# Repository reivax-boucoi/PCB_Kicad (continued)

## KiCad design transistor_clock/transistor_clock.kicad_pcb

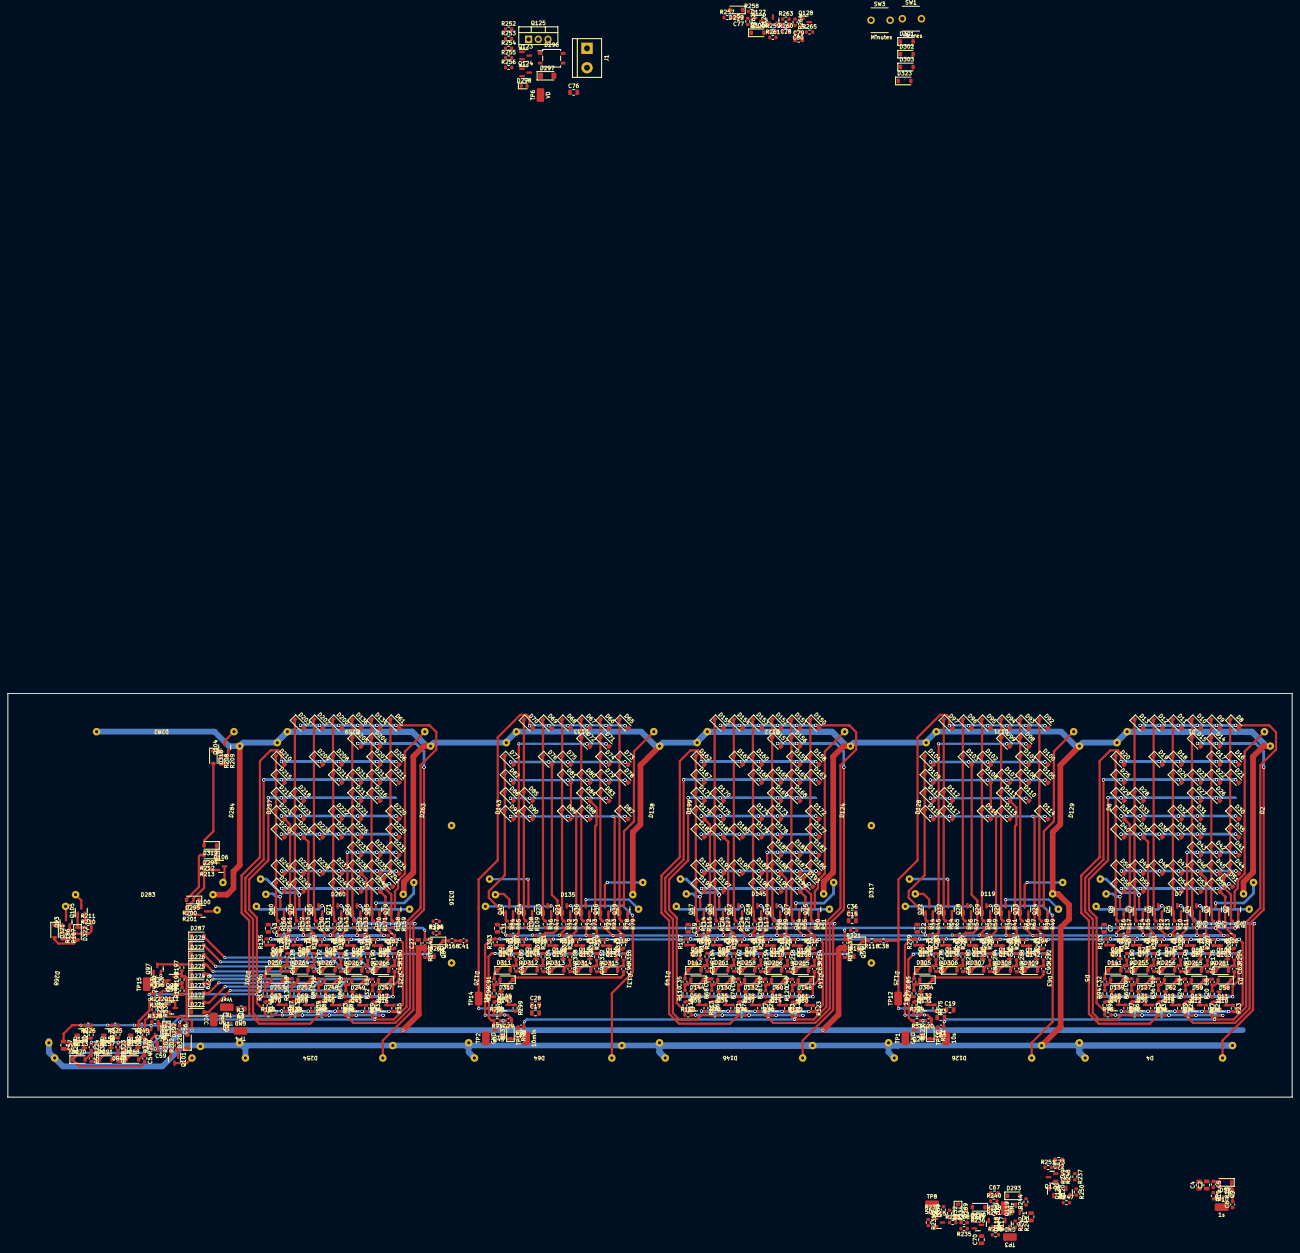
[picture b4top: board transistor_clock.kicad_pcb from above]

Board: 2 copper layers, 336.5 x 105.8 mm, 907 parts (0 on the bottom side), 423 nets.

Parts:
C1, C2, C4, C7, C13, C15, C17, C19, C22, C27, C28, C31, C36, C39, C43, C57, C58, C67, C72, C76, C79: 10u; C_0805_2012Metric
C3, C8, C9, C10, C11, C12, C14, C16, C18, C23, C24, C25, C26, C32, C33, C34, C35, C40, C44, C45, C46, C47, C48, C49, C50, C51, C52, C53, C54, C55, C62, C63, C64, C85, C86, C87, C88, C89, C90, C91, C92, C93, C94, C95, C96: 1n; C_0603_1608Metric
C5, C6, C20, C21, C29, C30, C37, C38, C41, C42, C56, C59, C68, C69, C73, C80: 100n; C_0603_1608Metric
C70, C71: 1u; C_0805_2012Metric
C77: 10n; C_0805_2012Metric
C78: 220p; C_0805_2012Metric
D1, D2, D3, D4, D5, D6, D7, D63, D64, D119, D120, D121, D122, D124, D125, D126, D128, D129, D131, D133, D135, D138, D140, D143, D145, D146, D149, D199, D201, D251, D254, D257, D259, D260, D263, D268, D279, D280, D282, D283, D284, D316, D317: LED; LED_filament_38mm
D8, D9, D10, D11, D12, D13, D14, D15, D16, D17, D18, D19, D20, D21, D22, D23, D24, D25, D26, D27, D28, D29, D30, D31, D32, D33, D34, D35, D36, D37, D38, D39, D40, D41, D42, D43, D44, D45, D46, D47, D48, D49, D50, D51, D52, D53, D54, D55, D56, D57, D58, D59, D60, D61, D62, D65, D66, D67, D68, D69, D70, D71, D72, D73, D74, D75, D76, D77, D78, D79, D80, D81, D82, D83, D84, D85, D86, D87, D88, D89, D90, D91, D92, D93, D94, D95, D96, D97, D98, D99, D100, D101, D102, D103, D104, D105, D106, D107, D108, D109, D110, D111, D112, D113, D114, D115, D116, D117, D118, D123, D127, D130, D132, D134, D136, D137, D139, D141, D142, D144, D147, D148, D150, D151, D152, D153, D154, D155, D156, D157, D158, D159, D160, D161, D162, D163, D164, D165, D166, D167, D168, D169, D170, D171, D172, D173, D174, D175, D176, D177, D178, D179, D180, D181, D182, D183, D184, D185, D186, D187, D188, D189, D190, D191, D192, D193, D194, D195, D196, D197, D198, D200, D202, D203, D204, D205, D206, D207, D208, D209, D210, D211, D212, D213, D214, D215, D216, D217, D218, D219, D220, D221, D222, D223, D224, D225, D226, D227, D228, D229, D230, D231, D232, D233, D234, D235, D236, D237, D238, D239, D240, D241, D242, D243, D244, D245, D246, D247, D248, D249, D250, D252, D253, D255, D256, D258, D261, D262, D264, D265, D266, D267, D269, D270, D271, D272, D273, D274, D275, D276, D277, D278, D281, D285, D286, D287, D288, D289, D290, D291, D292, D293, D294, D295, D299, D300, D301, D302, D303, D304, D305, D306, D307, D308, D309, D310, D311, D312, D313, D314, D315, D318, D319, D320, D321, D322, D323: 1N4148W; D_SOD-123
D296: D_Bridge_+-AA; SO-4_4.4x4.3mm_P2.54mm
D297: D_Zener; D_MiniMELF
D298: LED; LED_0603_1608Metric
J1: Conn_01x02; TerminalBlock_bornier-2_P5.08mm
Q1, Q2, Q3, Q4, Q5, Q6, Q7, Q8, Q9, Q11, Q13, Q15, Q17, Q19, Q20, Q21, Q22, Q23, Q24, Q25, Q26, Q27, Q28, Q29, Q31, Q32, Q33, Q35, Q36, Q38, Q39, Q41, Q42, Q44, Q45, Q46, Q48, Q49, Q51, Q53, Q54, Q56, Q57, Q58, Q59, Q61, Q62, Q63, Q65, Q66, Q67, Q69, Q71, Q73, Q75, Q76, Q78, Q79, Q80, Q82, Q83, Q84, Q85, Q87, Q89, Q91, Q93, Q94, Q96, Q97, Q99, Q100, Q101, Q103, Q104, Q105, Q106, Q108, Q110, Q111, Q113, Q115, Q118, Q121, Q123, Q124, Q127, Q132, Q134, Q136, Q138, Q140, Q142, Q144, Q146, Q148, Q150, Q152, Q154, Q155, Q157, Q158: MMBT3904; SOT-23
Q10, Q12, Q14, Q16, Q18, Q30, Q34, Q37, Q40, Q43, Q47, Q50, Q52, Q55, Q60, Q64, Q68, Q70, Q72, Q74, Q77, Q81, Q86, Q88, Q90, Q92, Q95, Q98, Q102, Q107, Q109, Q112, Q114, Q116, Q117, Q119, Q120, Q122, Q126, Q128, Q131, Q133, Q135, Q137, Q139, Q141, Q143, Q145, Q147, Q149, Q151, Q153, Q156: MMBT5401; SOT-23
Q125: TIP41; TO-220-3_Vertical
R1: 3k9; R_0603_1608Metric
R2, R3, R5, R7, R9, R11, R13, R15, R17, R18, R21, R23, R25, R27, R29, R31, R33, R35, R37, R39, R41, R43, R45, R47, R49, R51, R52, R55, R57, R59, R61, R63, R65, R67, R69, R71, R73, R75, R77, R79, R81, R83, R85, R87, R89, R90, R93, R95, R97, R99, R101, R103, R105, R107, R109, R111, R113, R115, R117, R118, R121, R123, R125, R127, R129, R131, R133, R135, R137, R139, R141, R143, R145, R147, R149, R151, R153, R155, R157, R159, R161, R163, R165, R167, R168, R171, R173, R175, R177, R179, R181, R183, R185, R187, R189, R191, R193, R194, R195, R196, R199, R201, R203, R205, R207, R209, R211, R213, R215, R217, R219, R221, R225, R227, R229, R232, R233, R237, R238, R241, R246, R249, R251, R260, R262, R264, R265, R273, R275, R277, R279, R281, R283, R285, R287, R289, R291, R293, R295, R297, R299, R301, R303, R305, R307, R309, R311, R313, R315, R317, R319, R320, R321, R324, R326, R327, R328: 10k; R_0603_1608Metric
R4, R6, R8, R10, R12, R14, R16, R40, R42, R44, R46, R48, R50, R54, R56, R58, R64, R66, R72, R78, R84, R92, R98, R108, R114, R116, R124, R126, R130, R132, R142, R152, R158, R160, R170, R186, R198, R200, R202, R208, R210, R212, R222, R223, R230, R231, R239, R242, R247, R250, R257, R258, R259, R263, R330, R331: 100k; R_0603_1608Metric
R19, R20, R22, R24, R26, R28, R30, R32, R34, R36, R38, R53, R60, R62, R68, R70, R74, R76, R80, R82, R86, R88, R91, R94, R96, R100, R102, R104, R106, R110, R112, R119, R120, R122, R128, R134, R136, R138, R140, R144, R146, R148, R150, R154, R156, R162, R164, R166, R169, R172, R174, R176, R178, R180, R182, R184, R188, R190, R192, R197, R204, R206, R214, R216, R218, R220, R224, R226, R228, R235, R240, R243, R245, R248, R272, R274, R276, R278, R280, R282, R284, R286, R288, R290, R292, R294, R296, R298, R300, R302, R304, R306, R308, R310, R312, R314, R316, R318, R323, R325, R329: 2k2; R_0603_1608Metric
R234: 4.7k; R_0603_1608Metric
R236, R244, R255, R256, R261: 1k; R_0603_1608Metric
R252, R253, R254: 500; R_0603_1608Metric
SW1: Heures; SW_PUSH_6mm_2pins
SW3: Minutes; SW_PUSH_6mm_2pins
TP1, TP2, TP3, TP4: GND; RCSRCW_0C_testpoint_1206
TP5: VCC; RCSRCW_0C_testpoint_1206
TP6: VD; RCSRCW_0C_testpoint_1206
TP7: Vref; RCSRCW_0C_testpoint_1206
TP8: 50Hz; RCSRCW_0C_testpoint_1206
TP9: 5Hz; RCSRCW_0C_testpoint_1206
TP10: 1s; RCSRCW_0C_testpoint_1206
TP11: 10s; RCSRCW_0C_testpoint_1206
TP12: 1min; RCSRCW_0C_testpoint_1206
TP13: 10min; RCSRCW_0C_testpoint_1206
TP14: 1hr; RCSRCW_0C_testpoint_1206
TP15: 24_rst; RCSRCW_0C_testpoint_1206

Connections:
/5Hz: Q119.1 (B), R240.2, R241.1, TP9.1
/50Hz: Q128.3 (C), R230.1, R265.2, TP8.1
/Dot_H-M: D316.1 (K), R320.1
/Dot_M-S: D317.1 (K), R321.1
/Hours/24_rst: Q97.1 (B), R195.1, R196.2, TP15.1
/Hours/CLK: Q84.3 (C), R32.1, R80.1, R86.1, R128.1, R136.1, R140.1, R169.2, R172.1, R180.1, R184.1, R190.1
/Hours/Div24_t_A: D318.1 (K), Q104.1 (B), R208.1
/Hours/Div24_t_B: D294.1 (K), D319.1 (K), Q106.1 (B), R212.1
/Hours/Div24_t_C: D295.1 (K), Q100.1 (B), R200.1
/Hours/Div24_t_D: D320.1 (K), Q101.1 (B), R202.1
/Hours/Div24_t_E: D321.1 (K), Q93.1 (B), R186.1
/Hours/Div24_t_G: D322.1 (K), Q105.1 (B), R210.1
/Hours/Div24_u_A: D61.1 (K), D206.1 (K), D211.1 (K), D220.1 (K), D225.1 (K), D231.1 (K), D234.1 (K), D241.1 (K), Q79.1 (B), R158.1
/Hours/Div24_u_B: D134.1 (K), D204.1 (K), D207.1 (K), D212.1 (K), D216.1 (K), D232.1 (K), D235.1 (K), D242.1 (K), Q85.1 (B), R170.1
/Hours/Div24_u_C: D136.1 (K), D205.1 (K), D213.1 (K), D217.1 (K), D221.1 (K), D226.1 (K), D233.1 (K), D236.1 (K), D243.1 (K), Q66.1 (B), R132.1
/Hours/Div24_u_D: D200.1 (K), D208.1 (K), D214.1 (K), D222.1 (K), D227.1 (K), D237.1 (K), D244.1 (K), Q71.1 (B), R142.1
/Hours/Div24_u_E: D202.1 (K), D209.1 (K), D228.1 (K), D238.1 (K), Q65.1 (B), R130.1
/Hours/Div24_u_F: D203.1 (K), D218.1 (K), D223.1 (K), D229.1 (K), D239.1 (K), D245.1 (K), Q76.1 (B), R152.1
/Hours/Div24_u_G: D210.1 (K), D215.1 (K), D219.1 (K), D224.1 (K), D230.1 (K), D240.1 (K), D246.1 (K), Q80.1 (B), R160.1
/Hours/I0: C45.2, D247.1 (K), Q16.2 (E)
/Hours/I1: C3.2, D249.1 (K), D271.2 (A), Q43.2 (E)
/Hours/I2: C14.2, D248.1 (K), D272.2 (A), Q40.2 (E)
/Hours/I3: C11.2, D252.1 (K), D273.2 (A), Q68.2 (E)
/Hours/I4: C18.2, D253.1 (K), D274.2 (A), Q70.2 (E)
/Hours/I5: C26.2, D250.1 (K), D275.2 (A), Q64.2 (E)
/Hours/I6: C16.2, D264.1 (K), D276.2 (A), Q86.2 (E)
/Hours/I7: C44.2, D267.1 (K), D277.2 (A), Q92.2 (E)
/Hours/I8: C46.2, D269.1 (K), D278.2 (A), Q95.2 (E)
/Hours/I9: C51.2, D266.1 (K), D287.2 (A), Q90.2 (E)
/Hours/Ih0: C54.2, D270.1 (K), Q112.2 (E)
/Hours/Ih1: C52.2, D291.1 (K), Q156.2 (E)
/Hours/Ih2: C55.2, D288.1 (K), Q114.2 (E)
/Hours/O0: C56.1, D61.2 (A), D134.2 (A), D136.2 (A), D200.2 (A), D202.2 (A), D203.2 (A), Q17.2 (E), R33.2, R34.1
/Hours/O1: D204.2 (A), D205.2 (A), Q44.2 (E), R87.2, R88.1
/Hours/O2: D206.2 (A), D207.2 (A), D208.2 (A), D209.2 (A), D210.2 (A), Q41.2 (E), R81.2, R82.1
/Hours/O3: D211.2 (A), D212.2 (A), D213.2 (A), D214.2 (A), D215.2 (A), Q69.2 (E), R137.2, R138.1
/Hours/O4: D216.2 (A), D217.2 (A), D218.2 (A), D219.2 (A), Q83.2 (E), R141.2, R166.1, R222.2
/Hours/O5: D220.2 (A), D221.2 (A), D222.2 (A), D223.2 (A), D224.2 (A), Q67.2 (E), R129.2, R134.1
/Hours/O6: D225.2 (A), D226.2 (A), D227.2 (A), D228.2 (A), D229.2 (A), D230.2 (A), Q87.2 (E), R173.2, R174.1
/Hours/O7: D231.2 (A), D232.2 (A), D233.2 (A), Q94.2 (E), R185.2, R188.1
/Hours/O8: D234.2 (A), D235.2 (A), D236.2 (A), D237.2 (A), D238.2 (A), D239.2 (A), D240.2 (A), Q96.2 (E), R191.2, R192.1
/Hours/O9: D241.2 (A), D242.2 (A), D243.2 (A), D244.2 (A), D245.2 (A), D246.2 (A), Q91.2 (E), R181.2, R182.1
/Hours/Oh0: Q113.2 (E), R225.2, R226.1
/Hours/Oh1: D294.2 (A), D295.2 (A), Q157.2 (E), R324.2, R325.1
/Hours/Oh2: D318.2 (A), D319.2 (A), D320.2 (A), D321.2 (A), D322.2 (A), Q155.2 (E), R223.2, R229.2, R245.1
/Hours/SCR_stage10/RST: Q158.3 (C), R224.1, R228.1, R323.1, R329.2
/Minutes/10Decoder/1: D156.2 (A), D157.2 (A), Q15.2 (E), R29.2, R30.1
/Minutes/10Decoder/2: D158.2 (A), D159.2 (A), D160.2 (A), D161.2 (A), D162.2 (A), Q38.2 (E), R75.2, R76.1
/Minutes/10Decoder/3: D163.2 (A), D164.2 (A), D165.2 (A), D166.2 (A), D167.2 (A), Q35.2 (E), R69.2, R70.1
/Minutes/10Decoder/4: D168.2 (A), D169.2 (A), D170.2 (A), D171.2 (A), Q56.2 (E), R111.2, R112.1
/Minutes/10Decoder/5: D172.2 (A), D173.2 (A), D174.2 (A), D175.2 (A), D176.2 (A), Q53.2 (E), R105.2, R106.1
/Minutes/10Decoder/6: D177.2 (A), D178.2 (A), D179.2 (A), D180.2 (A), D181.2 (A), D182.2 (A), Q82.2 (E), R163.2, R164.1
/Minutes/10Decoder/7: D183.2 (A), D184.2 (A), D185.2 (A), Q78.2 (E), R155.2, R156.1
/Minutes/10Decoder/8: D186.2 (A), D187.2 (A), D188.2 (A), D189.2 (A), D190.2 (A), D191.2 (A), D192.2 (A), Q110.2 (E), R219.2, R220.1
/Minutes/10Decoder/9: D193.2 (A), D194.2 (A), D195.2 (A), D196.2 (A), D197.2 (A), D198.2 (A), Q108.2 (E), R215.2, R216.1
/Minutes/10counter/RST: Q59.3 (C), R28.1, R68.1, R74.1, R104.1, R110.1, R119.2, R120.1, R154.1, R162.1, R214.1, R218.1
/Minutes/10counter/SCR_stage1/NEXT: C10.2, D132.1 (K), Q37.2 (E)
/Minutes/10counter/SCR_stage2/NEXT: C25.2, D130.1 (K), Q34.2 (E)
/Minutes/10counter/SCR_stage3/NEXT: C24.2, D144.1 (K), Q55.2 (E)
/Minutes/10counter/SCR_stage4/NEXT: C35.2, D142.1 (K), Q52.2 (E)
/Minutes/10counter/SCR_stage5/NEXT: C34.2, D261.1 (K), Q81.2 (E)
/Minutes/10counter/SCR_stage6/NEXT: C50.2, D258.1 (K), Q77.2 (E)
/Minutes/10counter/SCR_stage7/NEXT: C49.2, D286.1 (K), Q109.2 (E)
/Minutes/10counter/SCR_stage8/NEXT: C64.2, D285.1 (K), Q107.2 (E)
/Minutes/10counter/SCR_stage/IN: C63.2, D148.1 (K), Q60.2 (E)
/Minutes/10counter/SCR_stage/NEXT: C40.2, D60.1 (K), Q14.2 (E)
/Minutes/Clk_in: C38.1, D301.1 (K), D302.1 (K)
/Minutes/Div10_A: D150.1 (K), D158.1 (K), D163.1 (K), D172.1 (K), D177.1 (K), D183.1 (K), D186.1 (K), D193.1 (K), Q25.1 (B), R50.1
/Minutes/Div10_B: D151.1 (K), D156.1 (K), D159.1 (K), D164.1 (K), D168.1 (K), D184.1 (K), D187.1 (K), D194.1 (K), Q27.1 (B), R54.1
/Minutes/Div10_C: D152.1 (K), D157.1 (K), D165.1 (K), D169.1 (K), D173.1 (K), D178.1 (K), D185.1 (K), D188.1 (K), D195.1 (K), Q49.1 (B), R98.1
/Minutes/Div10_D: D153.1 (K), D160.1 (K), D166.1 (K), D174.1 (K), D179.1 (K), D189.1 (K), D196.1 (K), Q58.1 (B), R116.1
/Minutes/Div10_E: D154.1 (K), D161.1 (K), D180.1 (K), D190.1 (K), Q62.1 (B), R124.1
/Minutes/Div10_F: D155.1 (K), D170.1 (K), D175.1 (K), D181.1 (K), D191.1 (K), D197.1 (K), Q63.1 (B), R126.1
/Minutes/Div10_G: D162.1 (K), D167.1 (K), D171.1 (K), D176.1 (K), D182.1 (K), D192.1 (K), D198.1 (K), Q57.1 (B), R114.1
/PSU/AC1: D296.3, J1.2
/PSU/AC2: D296.4, J1.1, R257.1
/Seconds/10Decoder/1: D14.2 (A), D15.2 (A), Q13.2 (E), R25.2, R26.1
/Seconds/10Decoder/2: D16.2 (A), D17.2 (A), D18.2 (A), D19.2 (A), D20.2 (A), Q19.2 (E), R37.2, R38.1
/Seconds/10Decoder/3: D21.2 (A), D22.2 (A), D23.2 (A), D24.2 (A), D25.2 (A), Q31.2 (E), R61.2, R62.1
/Seconds/10Decoder/4: D26.2 (A), D27.2 (A), D28.2 (A), D29.2 (A), Q48.2 (E), R95.2, R96.1
/Seconds/10Decoder/5: D30.2 (A), D31.2 (A), D32.2 (A), D33.2 (A), D34.2 (A), Q51.2 (E), R101.2, R102.1
/Seconds/10Decoder/6: D35.2 (A), D36.2 (A), D37.2 (A), D38.2 (A), D39.2 (A), D40.2 (A), Q73.2 (E), R145.2, R146.1
/Seconds/10Decoder/7: D41.2 (A), D42.2 (A), D43.2 (A), Q75.2 (E), R149.2, R150.1
/Seconds/10Decoder/8: D44.2 (A), D45.2 (A), D46.2 (A), D47.2 (A), D48.2 (A), D49.2 (A), D50.2 (A), Q89.2 (E), R177.2, R178.1
/Seconds/10Decoder/9: D51.2 (A), D52.2 (A), D53.2 (A), D54.2 (A), D55.2 (A), D56.2 (A), Q103.2 (E), R205.2, R206.1
/Seconds/10counter/RST: Q9.3 (C), R19.2, R20.1, R24.1, R36.1, R60.1, R94.1, R100.1, R144.1, R148.1, R176.1, R204.1
/Seconds/10counter/SCR_stage1/NEXT: C9.2, D62.1 (K), Q18.2 (E)
/Seconds/10counter/SCR_stage2/NEXT: C12.2, D127.1 (K), Q30.2 (E)
/Seconds/10counter/SCR_stage3/NEXT: C23.2, D139.1 (K), Q47.2 (E)
/Seconds/10counter/SCR_stage4/NEXT: C32.2, D141.1 (K), Q50.2 (E)
/Seconds/10counter/SCR_stage5/NEXT: C33.2, D255.1 (K), Q72.2 (E)
/Seconds/10counter/SCR_stage6/NEXT: C47.2, D256.1 (K), Q74.2 (E)
/Seconds/10counter/SCR_stage7/NEXT: C48.2, D265.1 (K), Q88.2 (E)
/Seconds/10counter/SCR_stage8/NEXT: C53.2, D281.1 (K), Q102.2 (E)
/Seconds/10counter/SCR_stage/IN: C62.2, D58.1 (K), Q10.2 (E)
/Seconds/10counter/SCR_stage/NEXT: C8.2, D59.1 (K), Q12.2 (E)
/Seconds/Div10_A: D8.1 (K), D16.1 (K), D21.1 (K), D30.1 (K), D35.1 (K), D41.1 (K), D44.1 (K), D51.1 (K), Q2.1 (B), R4.1
/Seconds/Div10_B: D9.1 (K), D14.1 (K), D17.1 (K), D22.1 (K), D26.1 (K), D42.1 (K), D45.1 (K), D52.1 (K), Q3.1 (B), R6.1
/Seconds/Div10_C: D10.1 (K), D15.1 (K), D23.1 (K), D27.1 (K), D31.1 (K), D36.1 (K), D43.1 (K), D46.1 (K), D53.1 (K), Q4.1 (B), R8.1
/Seconds/Div10_D: D11.1 (K), D18.1 (K), D24.1 (K), D32.1 (K), D37.1 (K), D47.1 (K), D54.1 (K), Q5.1 (B), R10.1
/Seconds/Div10_E: D12.1 (K), D19.1 (K), D38.1 (K), D48.1 (K), Q6.1 (B), R12.1
/Seconds/Div10_F: D13.1 (K), D28.1 (K), D33.1 (K), D39.1 (K), D49.1 (K), D55.1 (K), Q7.1 (B), R14.1
/Seconds/Div10_G: D20.1 (K), D25.1 (K), D29.1 (K), D34.1 (K), D40.1 (K), D50.1 (K), D56.1 (K), Q8.1 (B), R16.1
/TensMinutes/6Decoder/1: D71.2 (A), D72.2 (A), Q146.2 (E), R301.2, R302.1
/TensMinutes/6Decoder/2: D73.2 (A), D74.2 (A), D75.2 (A), D76.2 (A), D77.2 (A), Q148.2 (E), R305.2, R306.1
/TensMinutes/6Decoder/3: D78.2 (A), D79.2 (A), D80.2 (A), D81.2 (A), D82.2 (A), Q150.2 (E), R309.2, R310.1
/TensMinutes/6Decoder/4: D83.2 (A), D84.2 (A), D85.2 (A), D86.2 (A), Q152.2 (E), R313.2, R314.1
/TensMinutes/6Decoder/5: D87.2 (A), D88.2 (A), D89.2 (A), D90.2 (A), D91.2 (A), Q154.2 (E), R317.2, R318.1
/TensMinutes/6counter/RST: Q45.3 (C), R91.2, R296.1, R300.1, R304.1, R308.1, R312.1, R316.1
/TensMinutes/6counter/SCR_stage1/NEXT: C92.2, D312.1 (K), Q147.2 (E)
/TensMinutes/6counter/SCR_stage2/NEXT: C93.2, D313.1 (K), Q149.2 (E)
/TensMinutes/6counter/SCR_stage3/NEXT: C94.2, D314.1 (K), Q151.2 (E)
/TensMinutes/6counter/SCR_stage4/NEXT: C95.2, D315.1 (K), Q153.2 (E)
/TensMinutes/6counter/SCR_stage/IN: C96.2, D310.1 (K), Q143.2 (E)
/TensMinutes/6counter/SCR_stage/NEXT: C91.2, D311.1 (K), Q145.2 (E)
/TensMinutes/Div6_A: D65.1 (K), D73.1 (K), D78.1 (K), D87.1 (K), Q39.1 (B), R78.1
/TensMinutes/Div6_B: D66.1 (K), D71.1 (K), D74.1 (K), D79.1 (K), D83.1 (K), Q46.1 (B), R92.1
/TensMinutes/Div6_C: D67.1 (K), D72.1 (K), D80.1 (K), D84.1 (K), D88.1 (K), Q36.1 (B), R72.1
/TensMinutes/Div6_D: D68.1 (K), D75.1 (K), D81.1 (K), D89.1 (K), Q21.1 (B), R42.1
/TensMinutes/Div6_E: D69.1 (K), D76.1 (K), Q23.1 (B), R46.1
/TensMinutes/Div6_F: D70.1 (K), D85.1 (K), D90.1 (K), Q54.1 (B), R108.1
/TensMinutes/Div6_G: D77.1 (K), D82.1 (K), D86.1 (K), D91.1 (K), Q42.1 (B), R84.1
/TensSeconds/6Decoder/1: D98.2 (A), D99.2 (A), Q134.2 (E), R277.2, R278.1
/TensSeconds/6Decoder/2: D100.2 (A), D101.2 (A), D102.2 (A), D103.2 (A), D104.2 (A), Q136.2 (E), R281.2, R282.1
/TensSeconds/6Decoder/3: D105.2 (A), D106.2 (A), D107.2 (A), D108.2 (A), D109.2 (A), Q138.2 (E), R285.2, R286.1
/TensSeconds/6Decoder/4: D110.2 (A), D111.2 (A), D112.2 (A), D113.2 (A), Q140.2 (E), R289.2, R290.1
/TensSeconds/6Decoder/5: D114.2 (A), D115.2 (A), D116.2 (A), D117.2 (A), D118.2 (A), Q142.2 (E), R293.2, R294.1
/TensSeconds/6counter/RST: Q26.3 (C), R53.2, R272.1, R276.1, R280.1, R284.1, R288.1, R292.1
/TensSeconds/6counter/SCR_stage1/NEXT: C86.2, D306.1 (K), Q135.2 (E)
/TensSeconds/6counter/SCR_stage2/NEXT: C87.2, D307.1 (K), Q137.2 (E)
/TensSeconds/6counter/SCR_stage3/NEXT: C88.2, D308.1 (K), Q139.2 (E)
/TensSeconds/6counter/SCR_stage4/NEXT: C89.2, D309.1 (K), Q141.2 (E)
/TensSeconds/6counter/SCR_stage/IN: C90.2, D304.1 (K), Q131.2 (E)
/TensSeconds/6counter/SCR_stage/NEXT: C85.2, D305.1 (K), Q133.2 (E)
/TensSeconds/Div6_A: D92.1 (K), D100.1 (K), D105.1 (K), D114.1 (K), Q24.1 (B), R48.1
/TensSeconds/Div6_B: D93.1 (K), D98.1 (K), D101.1 (K), D106.1 (K), D110.1 (K), Q33.1 (B), R66.1
/TensSeconds/Div6_C: D94.1 (K), D99.1 (K), D107.1 (K), D111.1 (K), D115.1 (K), Q20.1 (B), R40.1
/TensSeconds/Div6_D: D95.1 (K), D102.1 (K), D108.1 (K), D116.1 (K), Q29.1 (B), R58.1
/TensSeconds/Div6_E: D96.1 (K), D103.1 (K), Q28.1 (B), R56.1
/TensSeconds/Div6_F: D97.1 (K), D112.1 (K), D117.1 (K), Q32.1 (B), R64.1
/TensSeconds/Div6_G: D104.1 (K), D109.1 (K), D113.1 (K), D118.1 (K), Q22.1 (B), R44.1
/Vref: C7.2, C22.2, C31.2, C39.2, C43.2, C57.2, Q1.2 (E), R3.1, R23.2, R27.2, R31.2, R35.2, R39.2, R63.2, R71.2, R77.2, R83.2, R89.2, R97.2, R103.2, R107.2, R113.2, R123.2, R135.2, R139.2, R147.2, R151.2, R157.2, R165.2, R167.2, R175.2, R179.2, R183.2, R189.2, R193.2, R207.2, R217.2, R221.2, R227.2, R246.2, R275.2, R279.2, R283.2, R287.2, R291.2, R295.2, R299.2, R303.2, R307.2, R311.2, R315.2, R319.2, R326.2, TP7.1
/clk_1hr: C41.1, D65.2 (A), D66.2 (A), D67.2 (A), D68.2 (A), D69.2 (A), D70.2 (A), D303.1 (K), D303.2 (A), D323.1 (K), Q144.2 (E), R297.2, R298.1, TP14.1
/clk_1min: D92.2 (A), D93.2 (A), D94.2 (A), D95.2 (A), D96.2 (A), D97.2 (A), D302.2 (A), Q132.2 (E), R273.2, R274.1, TP12.1
/clk_1s: C6.1, Q122.3 (C), R251.1, SW1.1, SW3.1, TP10.1
/clk_10min: C30.1, D150.2 (A), D151.2 (A), D152.2 (A), D153.2 (A), D154.2 (A), D155.2 (A), Q61.2 (E), R121.2, R122.1, TP13.1
/clk_10s: C21.1, D8.2 (A), D9.2 (A), D10.2 (A), D11.2 (A), D12.2 (A), D13.2 (A), Q11.2 (E), R21.2, R22.1, TP11.1
GND: C1.1, C2.2, C4.2, C5.1, C7.1, C13.2, C15.2, C17.2, C19.2, C20.1, C22.1, C27.2, C28.2, C29.1, C31.1, C36.2, C37.1, C39.1, C42.1, C43.1, C57.1, C58.2, C59.1, C67.2, C69.1, C70.1, C71.1, C72.2, C73.1, C76.2, C77.1, C79.2, C80.1, D57.2 (A), D123.2 (A), D137.2 (A), D147.2 (A), D262.2 (A), D292.2 (A), D296.2 (-), D297.2 (A), Q9.2 (E), Q26.2 (E), Q45.2 (E), Q59.2 (E), Q84.2 (E), Q97.2 (E), Q111.2 (E), Q115.2 (E), Q118.2 (E), Q121.2 (E), Q126.3 (C), Q158.2 (E), R2.2, R3.2, R4.2, R5.2, R6.2, R7.2, R8.2, R9.2, R10.2, R11.2, R12.2, R13.2, R14.2, R15.2, R16.2, R17.2, R22.2, R26.2, R30.2, R34.2, R38.2, R40.2, R41.2, R42.2, R43.2, R44.2, R45.2, R46.2, R47.2, R48.2, R49.2, R50.2, R51.2, R54.2, R55.2, R56.2, R57.2, R58.2, R59.2, R62.2, R64.2, R65.2, R66.2, R67.2, R70.2, R72.2, R73.2, R76.2, R78.2, R79.2, R82.2, R84.2, R85.2, R88.2, R92.2, R93.2, R96.2, R98.2, R99.2, R102.2, R106.2, R108.2, R109.2, R112.2, R114.2, R115.2, R116.2, R117.2, R122.2, R124.2, R125.2, R126.2, R127.2, R130.2, R131.2, R132.2, R133.2, R134.2, R138.2, R142.2, R143.2, R146.2, R150.2, R152.2, R153.2, R156.2, R158.2, R159.2, R160.2, R161.2, R164.2, R166.2, R170.2, R171.2, R174.2, R178.2, R182.2, R186.2, R187.2, R188.2, R192.2, R194.1, R196.1, R200.2, R201.2, R202.2, R203.2, R206.2, R208.2, R209.2, R210.2, R211.2, R212.2, R213.2, R216.2, R220.2, R226.2, R231.2, R239.2, R242.2, R245.2, R247.2, R250.2, R251.2, R255.2, R256.2, R262.1, R265.1, R274.2, R278.2, R282.2, R286.2, R290.2, R294.2, R298.2, R302.2, R306.2, R310.2, R314.2, R318.2, R320.2, R321.2, R325.2, R328.1, R330.2, R331.2, TP1.1, TP2.1, TP3.1, TP4.1
unnamed: C6.2, R18.1
unnamed: C21.2, R52.1
unnamed: C30.2, R90.1
unnamed: C38.2, R118.1
unnamed: C41.2, R168.1
unnamed: C56.2, R327.1
unnamed: C68.1, R233.2
unnamed: R252.2, R253.2
unnamed: D1.1 (K), Q2.3 (C)
unnamed: D2.1 (K), Q3.3 (C)
unnamed: D3.1 (K), Q4.3 (C)
unnamed: D4.1 (K), Q5.3 (C)
unnamed: D5.1 (K), Q6.3 (C)
unnamed: D6.1 (K), Q7.3 (C)
unnamed: D7.1 (K), Q8.3 (C)
unnamed: D57.1 (K), Q9.1 (B), R18.2
unnamed: C8.1, D58.2 (A), R20.2
unnamed: C9.1, D59.2 (A), R24.2
unnamed: C10.1, D60.2 (A), R28.2
unnamed: C12.1, D62.2 (A), R36.2
unnamed: D63.1 (K), Q20.3 (C)
unnamed: D64.1 (K), Q21.3 (C)
unnamed: D119.1 (K), Q22.3 (C)
unnamed: D120.1 (K), Q23.3 (C)
unnamed: D121.1 (K), Q24.3 (C)
unnamed: D122.1 (K), Q25.3 (C)
unnamed: D123.1 (K), Q26.1 (B), R52.2
unnamed: D124.1 (K), Q27.3 (C)
unnamed: D125.1 (K), Q28.3 (C)
unnamed: D126.1 (K), Q29.3 (C)
unnamed: C23.1, D127.2 (A), R60.2
unnamed: D128.1 (K), Q32.3 (C)
unnamed: D129.1 (K), Q33.3 (C)
unnamed: C24.1, D130.2 (A), R68.2
unnamed: D131.1 (K), Q36.3 (C)
unnamed: C25.1, D132.2 (A), R74.2
unnamed: D133.1 (K), Q39.3 (C)
unnamed: D135.1 (K), Q42.3 (C)
unnamed: D137.1 (K), Q45.1 (B), R90.2
unnamed: D138.1 (K), Q46.3 (C)
unnamed: C32.1, D139.2 (A), R94.2
unnamed: D140.1 (K), Q49.3 (C)
unnamed: C33.1, D141.2 (A), R100.2
unnamed: C34.1, D142.2 (A), R104.2
unnamed: D143.1 (K), Q54.3 (C)
unnamed: C35.1, D144.2 (A), R110.2
unnamed: D145.1 (K), Q57.3 (C)
unnamed: D146.1 (K), Q58.3 (C)
unnamed: D147.1 (K), Q59.1 (B), R118.2
unnamed: C40.1, D148.2 (A), R120.2
unnamed: D149.1 (K), Q62.3 (C)
unnamed: D199.1 (K), Q63.3 (C)
unnamed: D201.1 (K), Q65.3 (C)
unnamed: C3.1, D247.2 (A), R32.2
unnamed: C11.1, D248.2 (A), R80.2
unnamed: C14.1, D249.2 (A), R86.2
unnamed: C16.1, D250.2 (A), R128.2
unnamed: D251.1 (K), Q66.3 (C)
unnamed: C18.1, D252.2 (A), R136.2
unnamed: C26.1, D253.2 (A), R140.2
unnamed: D254.1 (K), Q71.3 (C)
unnamed: C47.1, D255.2 (A), R144.2
unnamed: C48.1, D256.2 (A), R148.2
unnamed: D257.1 (K), Q76.3 (C)
unnamed: C49.1, D258.2 (A), R154.2
unnamed: D259.1 (K), Q79.3 (C)
unnamed: D260.1 (K), Q80.3 (C)
unnamed: C50.1, D261.2 (A), R162.2
unnamed: D262.1 (K), Q84.1 (B), R168.2, R194.2
unnamed: D263.1 (K), Q85.3 (C)
unnamed: C44.1, D264.2 (A), R172.2
unnamed: C53.1, D265.2 (A), R176.2
unnamed: C45.1, D266.2 (A), R180.2
unnamed: C46.1, D267.2 (A), R184.2
unnamed: D268.1 (K), Q93.3 (C)
unnamed: C51.1, D269.2 (A), R190.2
unnamed: C52.1, D270.2 (A), R224.2
unnamed: D271.1 (K), D272.1 (K), D273.1 (K), D274.1 (K), D275.1 (K), D276.1 (K), D277.1 (K), D278.1 (K), D287.1 (K), Q97.3 (C), R197.2
unnamed: D279.1 (K), Q100.3 (C)
unnamed: D280.1 (K), Q101.3 (C)
unnamed: C62.1, D281.2 (A), R204.2
unnamed: D282.1 (K), Q104.3 (C)
unnamed: D283.1 (K), Q105.3 (C)
unnamed: D284.1 (K), Q106.3 (C)
unnamed: C63.1, D285.2 (A), R214.2
unnamed: C64.1, D286.2 (A), R218.2
unnamed: C54.1, D288.2 (A), R228.2
unnamed: C68.2, D289.2 (A), Q116.1 (B), R234.1
unnamed: D290.2 (A), R236.2
unnamed: D290.1 (K), Q117.2 (E)
unnamed: C55.1, D291.2 (A), R323.2
unnamed: D292.1 (K), Q158.1 (B), R327.2, R328.2
unnamed: D293.2 (A), R244.2
unnamed: D293.1 (K), Q120.2 (E)
unnamed: D296.1 (+), Q123.3 (C), Q125.2 (C), R252.1
unnamed: D297.1 (K), Q124.2 (E)
unnamed: D298.1 (K), R256.1
unnamed: C77.2, D299.2 (A), R257.2
unnamed: D299.1 (K), R258.1
unnamed: D300.2 (A), R261.1
unnamed: D300.1 (K), Q127.2 (E), R262.2
unnamed: D301.2 (A), SW3.2
unnamed: C85.1, D304.2 (A), R272.2
unnamed: C86.1, D305.2 (A), R276.2
unnamed: C87.1, D306.2 (A), R280.2
unnamed: C88.1, D307.2 (A), R284.2
unnamed: C89.1, D308.2 (A), R288.2
unnamed: C90.1, D309.2 (A), R292.2
unnamed: C91.1, D310.2 (A), R296.2
unnamed: C92.1, D311.2 (A), R300.2
unnamed: C93.1, D312.2 (A), R304.2
unnamed: C94.1, D313.2 (A), R308.2
unnamed: C95.1, D314.2 (A), R312.2
unnamed: C96.1, D315.2 (A), R316.2
unnamed: D323.2 (A), SW1.2
unnamed: C1.2, Q1.1 (B), R1.2, R2.1
unnamed: Q2.2 (E), R5.1
unnamed: Q3.2 (E), R7.1
unnamed: Q4.2 (E), R9.1
unnamed: Q5.2 (E), R11.1
unnamed: Q6.2 (E), R13.1
unnamed: Q7.2 (E), R15.1
unnamed: Q8.2 (E), R17.1
unnamed: Q10.1 (B), Q11.3 (C), R23.1
unnamed: Q10.3 (C), Q11.1 (B), R21.1
unnamed: Q12.1 (B), Q13.3 (C), R27.1
unnamed: Q12.3 (C), Q13.1 (B), R25.1
unnamed: Q14.1 (B), Q15.3 (C), R31.1
unnamed: Q14.3 (C), Q15.1 (B), R29.1
unnamed: Q16.1 (B), Q17.3 (C), R35.1
unnamed: Q16.3 (C), Q17.1 (B), R33.1
unnamed: Q18.1 (B), Q19.3 (C), R39.1
unnamed: Q18.3 (C), Q19.1 (B), R37.1
unnamed: Q20.2 (E), R41.1
unnamed: Q21.2 (E), R43.1
unnamed: Q22.2 (E), R45.1
unnamed: Q23.2 (E), R47.1
unnamed: Q24.2 (E), R49.1
unnamed: Q25.2 (E), R51.1
unnamed: Q27.2 (E), R55.1
unnamed: Q28.2 (E), R57.1
unnamed: Q29.2 (E), R59.1
unnamed: Q30.1 (B), Q31.3 (C), R63.1
unnamed: Q30.3 (C), Q31.1 (B), R61.1
unnamed: Q32.2 (E), R65.1
unnamed: Q33.2 (E), R67.1
unnamed: Q34.1 (B), Q35.3 (C), R71.1
unnamed: Q34.3 (C), Q35.1 (B), R69.1
unnamed: Q36.2 (E), R73.1
unnamed: Q37.1 (B), Q38.3 (C), R77.1
unnamed: Q37.3 (C), Q38.1 (B), R75.1
unnamed: Q39.2 (E), R79.1
unnamed: Q40.1 (B), Q41.3 (C), R83.1
unnamed: Q40.3 (C), Q41.1 (B), R81.1
unnamed: Q42.2 (E), R85.1
unnamed: Q43.1 (B), Q44.3 (C), R89.1
unnamed: Q43.3 (C), Q44.1 (B), R87.1
unnamed: Q46.2 (E), R93.1
unnamed: Q47.1 (B), Q48.3 (C), R97.1
unnamed: Q47.3 (C), Q48.1 (B), R95.1
unnamed: Q49.2 (E), R99.1
unnamed: Q50.1 (B), Q51.3 (C), R103.1
unnamed: Q50.3 (C), Q51.1 (B), R101.1
unnamed: Q52.1 (B), Q53.3 (C), R107.1
unnamed: Q52.3 (C), Q53.1 (B), R105.1
unnamed: Q54.2 (E), R109.1
unnamed: Q55.1 (B), Q56.3 (C), R113.1
unnamed: Q55.3 (C), Q56.1 (B), R111.1
unnamed: Q57.2 (E), R115.1
unnamed: Q58.2 (E), R117.1
unnamed: Q60.1 (B), Q61.3 (C), R123.1
unnamed: Q60.3 (C), Q61.1 (B), R121.1
unnamed: Q62.2 (E), R125.1
unnamed: Q63.2 (E), R127.1
unnamed: Q64.1 (B), Q67.3 (C), R135.1
unnamed: Q64.3 (C), Q67.1 (B), R129.1
unnamed: Q65.2 (E), R131.1
unnamed: Q66.2 (E), R133.1
unnamed: Q68.1 (B), Q69.3 (C), R139.1
unnamed: Q68.3 (C), Q69.1 (B), R137.1
unnamed: Q70.1 (B), Q83.3 (C), R167.1
unnamed: Q70.3 (C), Q83.1 (B), R141.1
unnamed: Q71.2 (E), R143.1
unnamed: Q72.1 (B), Q73.3 (C), R147.1
unnamed: Q72.3 (C), Q73.1 (B), R145.1
unnamed: Q74.1 (B), Q75.3 (C), R151.1
unnamed: Q74.3 (C), Q75.1 (B), R149.1
unnamed: Q76.2 (E), R153.1
unnamed: Q77.1 (B), Q78.3 (C), R157.1
unnamed: Q77.3 (C), Q78.1 (B), R155.1
unnamed: Q79.2 (E), R159.1
unnamed: Q80.2 (E), R161.1
unnamed: Q81.1 (B), Q82.3 (C), R165.1
unnamed: Q81.3 (C), Q82.1 (B), R163.1
unnamed: Q85.2 (E), R171.1
unnamed: Q86.1 (B), Q87.3 (C), R175.1
unnamed: Q86.3 (C), Q87.1 (B), R173.1
unnamed: Q88.1 (B), Q89.3 (C), R179.1
unnamed: Q88.3 (C), Q89.1 (B), R177.1
unnamed: Q90.1 (B), Q91.3 (C), R183.1
unnamed: Q90.3 (C), Q91.1 (B), R181.1
unnamed: Q92.1 (B), Q94.3 (C), R189.1
unnamed: Q92.3 (C), Q94.1 (B), R185.1
unnamed: Q93.2 (E), R187.1
unnamed: Q95.1 (B), Q96.3 (C), R193.1
unnamed: Q95.3 (C), Q96.1 (B), R191.1
unnamed: Q98.1 (B), R198.1, R199.2
unnamed: Q98.3 (C), R195.2
unnamed: Q99.1 (B), R222.1, R331.1
unnamed: Q99.3 (C), R199.1
unnamed: Q100.2 (E), R201.1
unnamed: Q101.2 (E), R203.1
unnamed: Q102.1 (B), Q103.3 (C), R207.1
unnamed: Q102.3 (C), Q103.1 (B), R205.1
unnamed: Q104.2 (E), R209.1
unnamed: Q105.2 (E), R211.1
unnamed: Q106.2 (E), R213.1
unnamed: Q107.1 (B), Q108.3 (C), R217.1
unnamed: Q107.3 (C), Q108.1 (B), R215.1
unnamed: Q109.1 (B), Q110.3 (C), R221.1
unnamed: Q109.3 (C), Q110.1 (B), R219.1
unnamed: Q111.1 (B), R223.1, R330.1
unnamed: Q99.2 (E), Q111.3 (C)
unnamed: Q112.1 (B), Q113.3 (C), R227.1
unnamed: Q112.3 (C), Q113.1 (B), R225.1
unnamed: Q114.1 (B), Q155.3 (C), R246.1
unnamed: Q114.3 (C), Q155.1 (B), R229.1
unnamed: Q115.1 (B), R230.2, R231.1
unnamed: Q115.3 (C), R232.2, R233.1
unnamed: C70.2, Q116.3 (C), R236.1
unnamed: Q116.2 (E), R235.1
unnamed: Q117.1 (B), Q118.3 (C), R238.2, R242.1
unnamed: Q117.3 (C), Q118.1 (B), R239.1
unnamed: C71.2, Q119.3 (C), R244.1
unnamed: Q119.2 (E), R243.1
unnamed: Q120.1 (B), Q121.3 (C), R237.2, R250.1
unnamed: Q120.3 (C), Q121.1 (B), R247.1
unnamed: Q122.1 (B), R248.2, R249.1
unnamed: Q123.1 (B), Q124.3 (C), R253.1
unnamed: Q123.2 (E), Q125.1 (B)
unnamed: Q124.1 (B), R254.2, R255.1
unnamed: Q126.1 (B), Q127.3 (C), R259.1
unnamed: C78.2, Q126.2 (E), R259.2, R260.1, R261.2, R263.1
unnamed: Q127.1 (B), R258.2
unnamed: C78.1, Q128.1 (B), R263.2, R264.1
unnamed: Q131.1 (B), Q132.3 (C), R275.1
unnamed: Q131.3 (C), Q132.1 (B), R273.1
unnamed: Q133.1 (B), Q134.3 (C), R279.1
unnamed: Q133.3 (C), Q134.1 (B), R277.1
unnamed: Q135.1 (B), Q136.3 (C), R283.1
unnamed: Q135.3 (C), Q136.1 (B), R281.1
unnamed: Q137.1 (B), Q138.3 (C), R287.1
unnamed: Q137.3 (C), Q138.1 (B), R285.1
unnamed: Q139.1 (B), Q140.3 (C), R291.1
unnamed: Q139.3 (C), Q140.1 (B), R289.1
unnamed: Q141.1 (B), Q142.3 (C), R295.1
unnamed: Q141.3 (C), Q142.1 (B), R293.1
unnamed: Q143.1 (B), Q144.3 (C), R299.1
unnamed: Q143.3 (C), Q144.1 (B), R297.1
unnamed: Q145.1 (B), Q146.3 (C), R303.1
unnamed: Q145.3 (C), Q146.1 (B), R301.1
unnamed: Q147.1 (B), Q148.3 (C), R307.1
unnamed: Q147.3 (C), Q148.1 (B), R305.1
unnamed: Q149.1 (B), Q150.3 (C), R311.1
unnamed: Q149.3 (C), Q150.1 (B), R309.1
unnamed: Q151.1 (B), Q152.3 (C), R315.1
unnamed: Q151.3 (C), Q152.1 (B), R313.1
unnamed: Q153.1 (B), Q154.3 (C), R319.1
unnamed: Q153.3 (C), Q154.1 (B), R317.1
unnamed: Q156.1 (B), Q157.3 (C), R326.1
unnamed: Q156.3 (C), Q157.1 (B), R324.1
unnamed: R237.1, R249.2
unnamed: R238.1, R241.2
VCC: C2.1, C4.1, C5.2, C13.1, C15.1, C17.1, C19.1, C20.2, C27.1, C28.1, C29.2, C36.1, C37.2, C42.2, C58.1, C59.2, C67.1, C69.2, C72.1, C73.2, C76.1, C79.1, C80.2, D289.1 (K), D298.2 (A), Q1.3 (C), Q98.2 (E), Q122.2 (E), Q125.3 (E), Q128.2 (E), R1.1, R19.1, R53.1, R91.1, R119.1, R169.1, R197.1, R198.2, R232.1, R234.2, R240.1, R248.1, R260.2, R264.2, R329.1, TP5.1
VD: D1.2 (A), D2.2 (A), D3.2 (A), D4.2 (A), D5.2 (A), D6.2 (A), D7.2 (A), D63.2 (A), D64.2 (A), D119.2 (A), D120.2 (A), D121.2 (A), D122.2 (A), D124.2 (A), D125.2 (A), D126.2 (A), D128.2 (A), D129.2 (A), D131.2 (A), D133.2 (A), D135.2 (A), D138.2 (A), D140.2 (A), D143.2 (A), D145.2 (A), D146.2 (A), D149.2 (A), D199.2 (A), D201.2 (A), D251.2 (A), D254.2 (A), D257.2 (A), D259.2 (A), D260.2 (A), D263.2 (A), D268.2 (A), D279.2 (A), D280.2 (A), D282.2 (A), D283.2 (A), D284.2 (A), D316.2 (A), D317.2 (A), TP6.1

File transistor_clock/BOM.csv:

Designator	Comment	Footprint	LCSC Part number
C36,C31,C19,C60,C17,C57,C2,C4,C28,C22,C58,C76,C67,C72,C43,C39,C27,C7,C79,C13,C61,C15,C1	10u	Capacitor_SMD:C_0805_2012Metric	C15850
C34,C14,C52,C94,C85,C95,C12,C62,C55,C44,C50,C88,C91,C49,C87,C16,C63,C25,C53,C26,C23,C11,C51,C8,C64,C9,C93,C48,C24,C92,C90,C89,C18,C3,C54,C46,C96,C35,C45,C40,C10,C32,C33,C86,C47	1n	Capacitor_SMD:C_0603_1608Metric	C1588
C29,C20,C42,C59,C73,C80,C37,C68,C38,C30,C56,C41,C21,C5,C6,C69,C77	100n	Capacitor_SMD:C_0603_1608Metric	C14663
D38,D72,D291,D203,D108,D187,D49,D240,D289,D166,D191,D27,D70,D15,D302,D20,D274,D208,D93,D107,D65,D319,D89,D170,D24,D197,D21,D33,D92,D97,D54,D296,D22,D200,D78,D101,D307,D130,D309,D247,D167,D231,D152,D275,D217,D262,D196,D308,D305,D221,D290,D235,D213,D232,D270,D314,D228,D25,D315,D77,D32,D82,D277,D306,D278,D310,D13,D37,D226,D320,D144,D136,D178,D110,D287,D162,D294,D169,D236,D19,D171,D8,D172,D220,D150,D325,D156,D323,D173,D53,D52,D88,D281,D322,D234,D230,D23,D193,D299,D215,D288,D224,D222,D312,D36,D253,D28,D261,D59,D141,D318,D42,D293,D212,D16,D183,D47,D154,D71,D11,D198,D68,D56,D286,D180,D324,D75,D188,D160,D192,D41,D98,D159,D272,D205,D115,D148,D239,D273,D298,D106,D114,D137,D175,D206,D116,D40,D246,D100,D158,D61,D132,D248,D292,D243,D99,D74,D44,D211,D214,D84,D168,D112,D227,D151,D255,D176,D327,D267,D242,D189,D39,D249,D45,D276,D295,D18,D147,D111,D80,D216,D153,D103,D94,D113,D87,D241,D179,D127,D81,D233,D117,D185,D326,D96,D229,D73,D300,D69,D118,D258,D245,D83,D95,D181,D252,D303,D238,D102,D186,D269,D218,D313,D177,D34,D174,D104,D142,D57,D321,D223,D155,D123,D301,D90,D184,D210,D67,D48,D161,D50,D105,D164,D256,D195,D271,D86,D204,D311,D194,D12,D51,D237,D265,D30,D190,D266,D225,D207,D76,D9,D66,D85,D244,D163,D202,D55,D26,D60,D58,D43,D182,D304,D79,D157,D91,D264,D109,D285,D14,D219,D35,D209,D134,D139,D31,D46,D17,D250,D62,D165,D29,D10	1N4148W	Diode_SMD:D_SOD-123	C81598
Q28,Q157,Q87,Q39,Q105,Q15,Q65,Q144,Q78,Q127,Q83,Q146,Q38,Q99,Q19,Q3,Q85,Q104,Q79,Q76,Q36,Q23,Q73,Q48,Q82,Q32,Q150,Q89,Q113,Q63,Q136,Q71,Q66,Q56,Q4,Q53,Q49,Q106,Q44,Q21,Q54,Q84,Q51,Q155,Q9,Q67,Q91,Q75,Q57,Q100,Q111,Q35,Q31,Q7,Q132,Q115,Q140,Q110,Q94,Q148,Q69,Q42,Q17,Q20,Q108,Q5,Q2,Q6,Q118,Q24,Q152,Q22,Q121,Q8,Q41,Q11,Q27,Q45,Q26,Q62,Q154,Q1,Q142,Q158,Q103,Q80,Q25,Q124,Q13,Q96,Q33,Q29,Q93,Q101,Q46,Q134,Q58,Q97,Q59,Q61,Q138	MMBT5551	Package_TO_SOT_SMD:SOT-23	C2145
Q133,Q147,Q120,Q77,Q16,Q153,Q37,Q143,Q12,Q126,Q149,Q131,Q72,Q90,Q30,Q156,Q64,Q107,Q139,Q68,Q60,Q47,Q135,Q112,Q18,Q86,Q98,Q92,Q14,Q50,Q81,Q141,Q102,Q151,Q145,Q88,Q122,Q137,Q74,Q109,Q119,Q34,Q40,Q116,Q114,Q52,Q55,Q95,Q70,Q117,Q43,Q10,Q128	MMBT5401	Package_TO_SOT_SMD:SOT-23	C8326
R113,R233,R205,R307,R90,R211,R177,R221,R99,R201,R143,R3,R189,R13,R171,R5,R17,R155,R61,R115,R27,R168,R149,R7,R31,R275,R45,R309,R101,R273,R289,R47,R321,R39,R85,R196,R241,R319,R123,R328,R79,R43,R262,R217,R264,R145,R249,R18,R95,R117,R89,R175,R127,R29,R181,R213,R163,R287,R81,R227,R35,R15,R37,R187,R303,R301,R52,R109,R194,R131,R121,R324,R69,R283,R238,R173,R199,R93,R51,R277,R254,R193,R77,R185,R105,R237,R71,R9,R133,R11,R57,R295,R157,R207,R151,R135,R97,R63,R281,R232,R179,R141,R297,R2,R215,R83,R59,R67,R103,R293,R65,R219,R125,R75,R195,R161,R251,R73,R183,R118,R111,R159,R41,R167,R317,R313,R299,R147,R246,R139,R315,R291,R21,R25,R87,R23,R265,R320,R137,R153,R260,R165,R279,R33,R327,R203,R209,R55,R326,R229,R305,R225,R191,R311,R285,R129,R49,R107	10k	Resistor_SMD:R_0603_1608Metric	C25804
R170,R186,R132,R126,R64,R250,R331,R66,R231,R92,R16,R8,R78,R14,R247,R257,R198,R42,R44,R114,R158,R239,R108,R259,R50,R256,R48,R72,R330,R263,R12,R46,R56,R200,R54,R230,R124,R10,R142,R98,R4,R160,R212,R116,R202,R258,R208,R40,R242,R152,R266,R210,R130,R223,R84,R58,R222,R6	100k	Resistor_SMD:R_0603_1608Metric	C25803
R91,R214,R300,R138,R243,R318,R226,R110,R136,R306,R272,R298,R162,R182,R280,R24,R140,R106,R178,R60,R102,R190,R276,R164,R34,R172,R80,R284,R19,R28,R228,R120,R302,R122,R286,R180,R204,R224,R128,R220,R316,R240,R323,R184,R290,R197,R26,R169,R88,R76,R308,R216,R96,R68,R150,R148,R314,R310,R166,R144,R296,R292,R176,R30,R278,R70,R20,R146,R188,R252,R156,R329,R32,R288,R206,R192,R22,R100,R112,R119,R53,R174,R245,R255,R82,R282,R134,R36,R104,R312,R94,R38,R325,R86,R218,R294,R74,R304,R154,R274,R62,R248,R235	2k2	Resistor_SMD:R_0603_1608Metric	C4190
R236, R244, R261	1k	Resistor_SMD:R_0603_1608Metric	C21190
